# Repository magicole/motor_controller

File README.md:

# motor_controller
Hardware design for a motor controller board with feedback

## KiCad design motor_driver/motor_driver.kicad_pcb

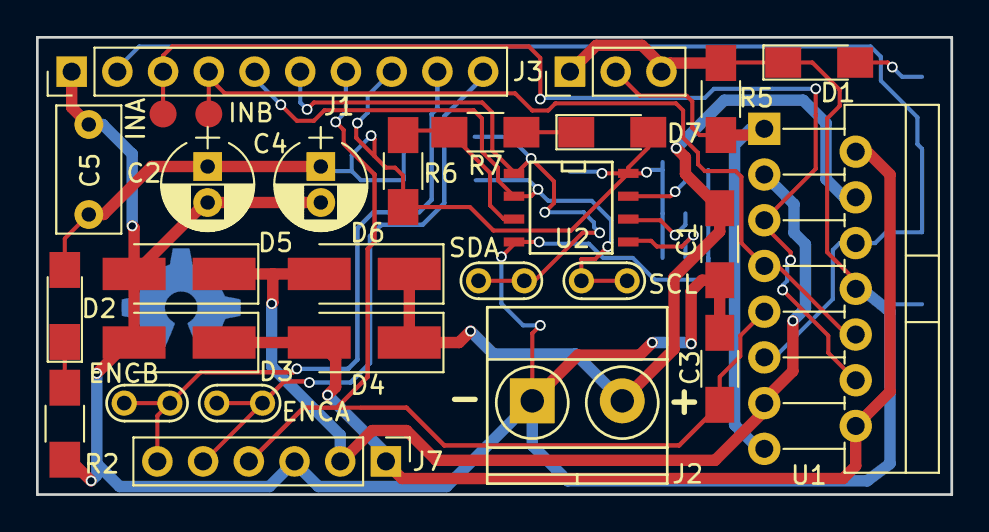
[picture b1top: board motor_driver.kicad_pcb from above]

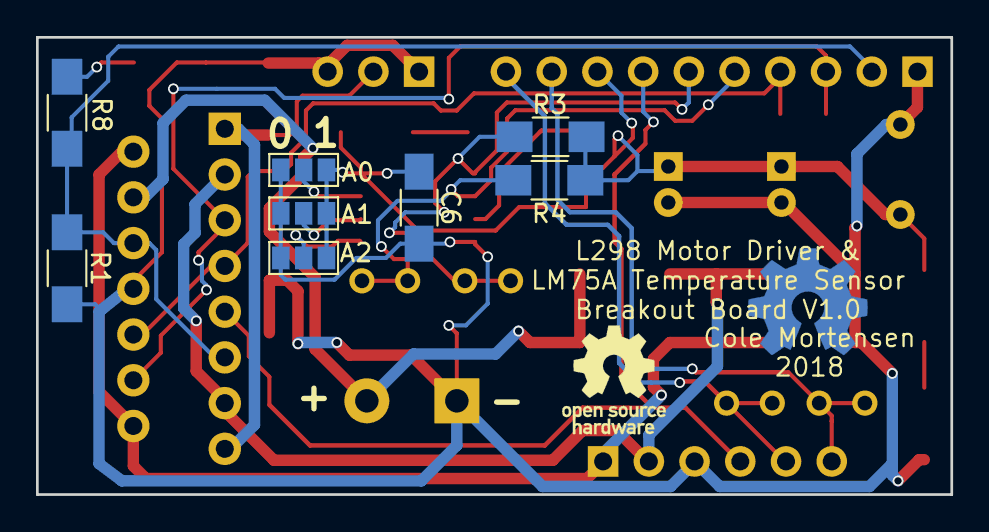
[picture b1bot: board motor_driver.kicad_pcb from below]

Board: 2 copper layers, 50.8 x 25.4 mm, 36 parts (8 on the bottom side), 21 nets.

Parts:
A0, A1, A2: GS3
C1, C3, C6: 100nF; C_1206_HandSoldering
C2, C4: 1uF; CP_Radial_D5.0mm_P2.00mm
C5: 10uF; C_Rect_L7.0mm_W3.5mm_P5.00mm
D1, D2, D7: LED; LED_1206_HandSoldering
D3, D4, D5, D6: D; D_SMA_Handsoldering
ENCA: ENC A; Test_Point
ENCB: ENC B; Test_Point
INA: IN A; Measurement_Point_Round-SMD-Pad_Small
INB: IN B; Measurement_Point_Round-SMD-Pad_Small
J1: Conn_01x10; Socket_Strip_Straight_1x10_Pitch2.54mm
J2: Screw_Terminal_01x02; TerminalBlock_Phoenix_MKDS1.5-2pol
J3: Conn_01x03; Socket_Strip_Straight_1x03_Pitch2.54mm
J7: Conn_01x06; Socket_Strip_Straight_1x06_Pitch2.54mm
R1, R3, R4, R6: 10K; R_1206_HandSoldering
R2, R7, R8: 470; R_1206_HandSoldering
R5: 0.04; R_1206_HandSoldering
SCL: SCL; Test_Point
SDA: SDA; Test_Point
U1: L298; TO-220-15_Vertical_StaggeredType1
U2: LM75A; SOIC-8-N

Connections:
GND: A0.1, A1.1, A2.1, C1.2, C2.2, C3.1, C4.2, C5.2, C6.2, D1.1, D3.2, D5.2, J1.1, J2.1, J3.1, J3.3, J7.3, R1.2, R2.2, R5.2, U1.8, U2.4
unnamed: C1.1, D4.1, D6.1, J2.2, U1.4
unnamed: A0.3, A1.3, A2.3, C2.1, C4.1, C5.1, C6.1, D2.2, D7.2, J1.8, R3.1, R4.1, R6.1, U2.8
unnamed: C3.2, J1.7, J7.4, U1.9
unnamed: D1.2, R8.2
unnamed: D2.1, R2.1
unnamed: D3.1, D4.2, J7.1, U1.2, U1.14
unnamed: D5.1, D6.2, J7.2, U1.3, U1.13
unnamed: D7.1, R7.1
unnamed: J1.2, R1.1, R8.1, U1.6, U1.11
unnamed: INA.1, J1.3, U1.5, U1.12
unnamed: INB.1, J1.4, U1.7, U1.10
unnamed: J1.5, R4.2, SCL.1, U2.2
unnamed: J1.6, R3.2, SDA.1, U2.1
unnamed: ENCB.1, J1.9, J7.6
unnamed: ENCA.1, J1.10, J7.5
unnamed: J3.2, R5.1, U1.1, U1.15
unnamed: A0.2, U2.7
unnamed: A1.2, U2.6
unnamed: A2.2, U2.5
unnamed: R6.2, R7.2, U2.3

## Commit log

2018-01-10 general placement done, needs resistors and capacitors
2018-01-11 added power caps and pull resistors
2018-01-22 basic board layout done
2018-02-08 routing finished, need to do silkscreen
2018-02-11 silkscreen finalized
